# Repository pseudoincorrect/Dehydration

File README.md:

<h1 align="center">Dehydration Measurement System</h1>

# Quick Description

PCB, Embedded system firmware and complementary GUI to measure the vital signs of a group of individuals.
<br>
This project's code "Dehydration" is due to the final objective to analyze data and display a dehydration level of the user. 
<br>
(Machine Learning involved, from the data science department) 
<br>

# Details

This system enable us to measure different various physical values of a group of subjects and record/display them on desktop application. The values measured are skin temperature, surrounding humidity and surrounding temperature.
<br>

## Embedded System and PCB
The embedded system communicates with bluetooth LE to a base station connected to a computer. 
<br>
It uses the Nordic NRF SDK and acts as a beacon to transmit data at regular intervals.
<br>
The PCB has been made with Eagle and assembled on premises. 
<br><br>

<br>

## GUI
The GUI is designed with Qt, PyQt more especially. 
<br>
It will search through the USB port for a base station and start receiving data when connected.
<br>
Data is then stored and displayed. The Devices are appearing and disapearing dynamically along their connections status.
<br>
Not the most elaborate UI, but it did a fine job back then and validated our proof of concept.
<br><br>

# Note
This project is the first version/prototype as proof of concept which lead us to continue on a following project with a higher complexity and capabilities.

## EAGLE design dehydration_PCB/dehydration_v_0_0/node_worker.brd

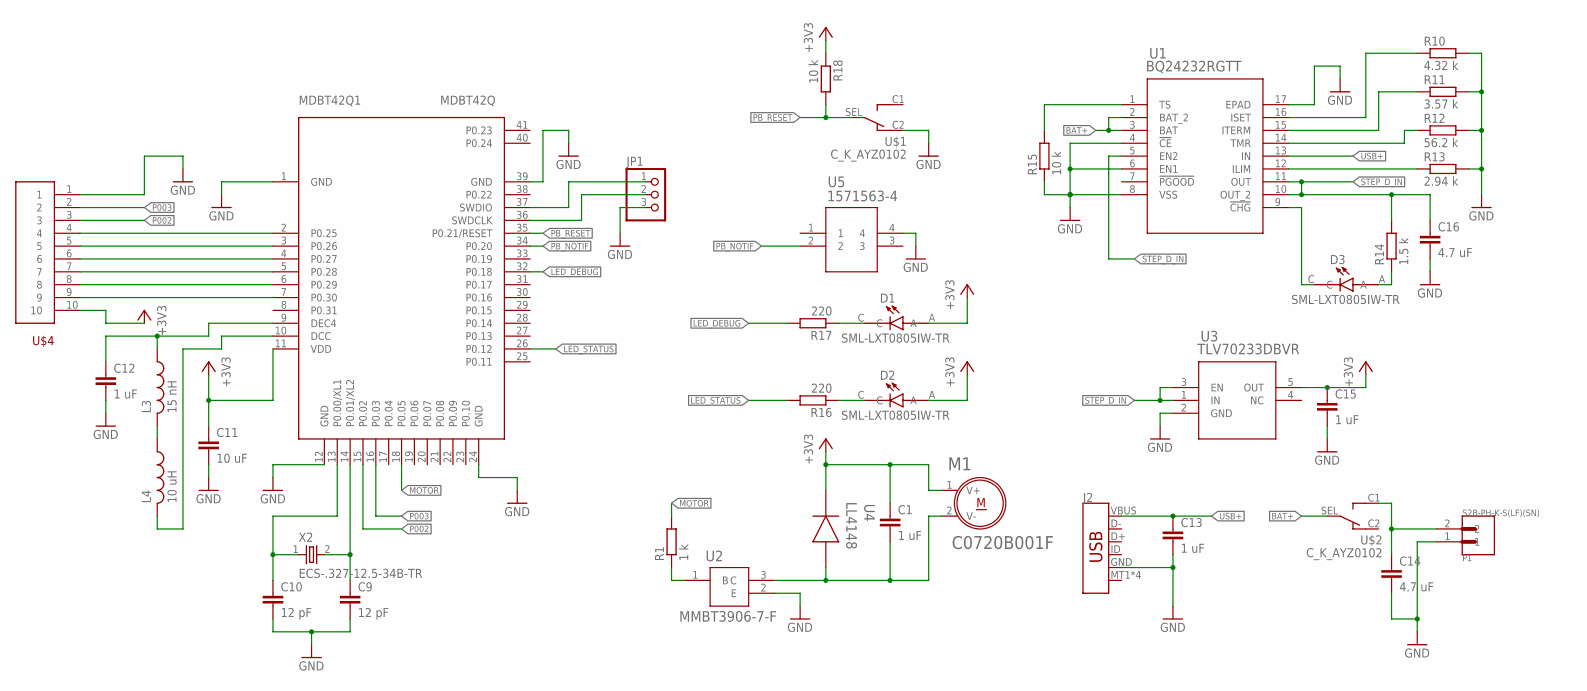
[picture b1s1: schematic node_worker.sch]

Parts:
C1, C12, C13, C15: 1 uF; C0603
C9, C10: 12 pF; C0603
C11: 10 uF; C0603
C14, C16: 4.7 uF; C0603
D1, D2, D3: SML-LXT0805IW-TR; LEDC2012X120N
J2: USB_MICRO-B_SMT; USB-MICROB
JP1: PINHD-1X3; 1X03
L3: 15 nH; L0603
L4: 10 uH; L0603
M1: C0720B001F; XDCR_C0720B001F
MDBT42Q1: MDBT42Q
P1: S2B-PH-K-S(LF)(SN); JST_S2B-PH-K-S(LF)(SN)
R1: 1 k; R0603
R10: 4.32 k; R0603
R11: 3.57 k; R0603
R12: 56.2 k; R0603
R13: 2.94 k; R0603
R14: 1.5 k; R0603
R15, R18: 10 k; R0603
R16, R17: 220; R0603
U1: BQ24232RGTT; RGT16_1P7X1P7
U2: MMBT3906-7-F; SOT-23
U3: TLV70233DBVR; DBV5
U4: LL4148; SOD-80
U5: 1571563-4; SWITCH_1571563-4
U$1, U$2: C_K_AYZ0102
U$4: MOLEX_FPC_10
X2: ECS-.327-12.5-34B-TR; XTAL_ECS-.327-12.5-34B-C-TR

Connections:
+3V3: C1.1, C11.1, C15.1, D1.A, D2.A, M1.1 (V+), MDBT42Q1.11 (VDD), R18.1, U3.5 (OUT), U4.CATH, U$4.10
BAT+: U1.2 (BAT_2), U1.3 (BAT), U$2.SEL
GND: C9.2, C10.2, C11.2, C12.2, C13.2, C14.2, C15.2, C16.2, J2.GND, JP1.3, MDBT42Q1.1 (GND), MDBT42Q1.12 (GND), MDBT42Q1.24 (GND), MDBT42Q1.39 (GND), P1.1, R10.2, R11.2, R12.2, R13.2, R15.1, U1.4 (!CE), U1.6 (EN1), U1.8 (VSS), U1.17 (EPAD), U2.2 (E), U3.2 (GND), U5.4, U$1.C2, U$4.1
LED_DEBUG: MDBT42Q1.32 (P0.18), R17.2
LED_STATUS: MDBT42Q1.26 (P0.12), R16.2
MOTOR: MDBT42Q1.18 (P0.05), R1.2
unnamed: C9.1, MDBT42Q1.14 (P0.01/XL2), X2.2
unnamed: L4.2, MDBT42Q1.10 (DCC)
unnamed: L3.2, L4.1
unnamed: R11.1, U1.15 (ITERM)
unnamed: C10.1, MDBT42Q1.13 (P0.00/XL1), X2.1
unnamed: JP1.2, MDBT42Q1.36 (SWDCLK)
unnamed: JP1.1, MDBT42Q1.37 (SWDIO)
unnamed: MDBT42Q1.7 (P0.30), U$4.9
unnamed: MDBT42Q1.6 (P0.29), U$4.8
unnamed: MDBT42Q1.5 (P0.28), U$4.7
unnamed: D1.C, R17.1
unnamed: D3.C, U1.9 (!CHG)
unnamed: R13.1, U1.12 (ILIM)
unnamed: C12.1, L3.1, MDBT42Q1.9 (DEC4)
unnamed: D3.A, R14.1
unnamed: R12.1, U1.14 (TMR)
unnamed: D2.C, R16.1
unnamed: R10.1, U1.16 (ISET)
unnamed: R15.2, U1.1 (TS)
unnamed: C14.1, P1.2, U$2.C1
unnamed: R1.1, U2.1 (B)
unnamed: MDBT42Q1.4 (P0.27), U$4.6
unnamed: C1.2, M1.2 (V-), U2.3 (C), U4.ANO
unnamed: MDBT42Q1.3 (P0.26), U$4.5
unnamed: MDBT42Q1.2 (P0.25), U$4.4
P002: MDBT42Q1.15 (P0.02), U$4.3
P003: MDBT42Q1.16 (P0.03), U$4.2
PB_NOTIF: MDBT42Q1.34 (P0.20), U5.2
PB_RESET: MDBT42Q1.35 (P0.21/RESET), R18.2, U$1.SEL
STEP_D_IN: C16.1, R14.2, U1.5 (EN2), U1.10 (OUT_2), U1.11 (OUT), U3.1 (IN), U3.3 (EN)
USB+: C13.1, J2.VBUS, U1.13 (IN)

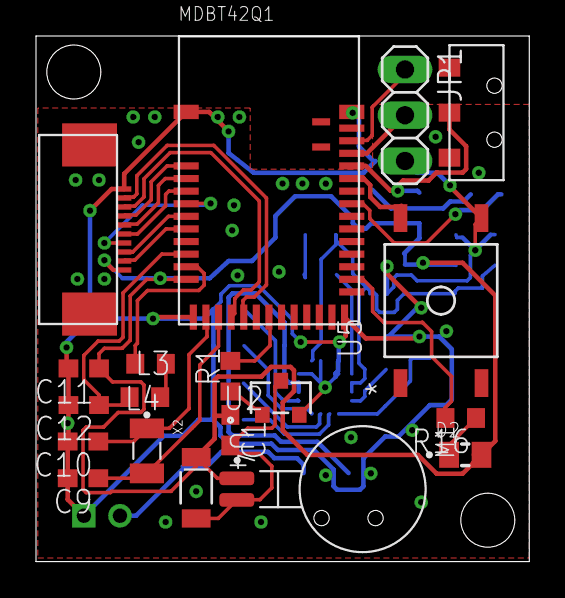
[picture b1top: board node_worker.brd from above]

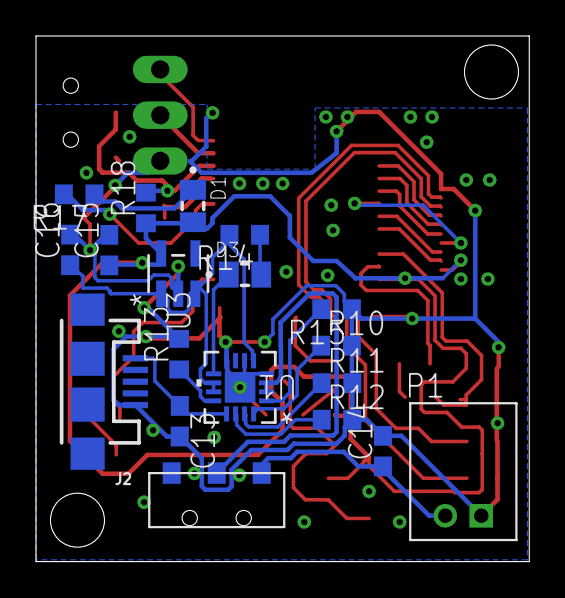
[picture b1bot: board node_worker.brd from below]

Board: 2 copper layers, 27.4 x 29.2 mm, 38 parts (19 on the bottom side), 37 nets.

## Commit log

2021-04-13 Added a Readme
2021-04-13 license and image path
2021-04-13 Added PCB files

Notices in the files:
README.md:
License: MIT
parts and their libraries:
SparkFun-Connectors: Licensing: Creative Commons ShareAlike 4.0 International - https://creativecommons.org/licenses/by-sa/4.0
